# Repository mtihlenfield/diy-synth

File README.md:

# Library of DIY Eurorack Modules

## Completed Modules:

- mixer - Simple buffered mixer
- mulitple - Simple buffered multiple
- noise - Noise generater module - Based on moritz klien's design
- keyboard - Volt per octave keyboard and sequencer
- power-supply - -+12V power supply

## In progress

- Attenuverter
- VCLFO

## Future Modules:

- quantizer - Digital quantizer
- Sample and Hold
- Slew Limiter

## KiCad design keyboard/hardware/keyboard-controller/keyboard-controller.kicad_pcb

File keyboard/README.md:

# CV/Gate Keyboard

An attempt at implementing a CV/Gate keyboard using a raspberry pi pico and an old keybed from a Yamaha PSS-560

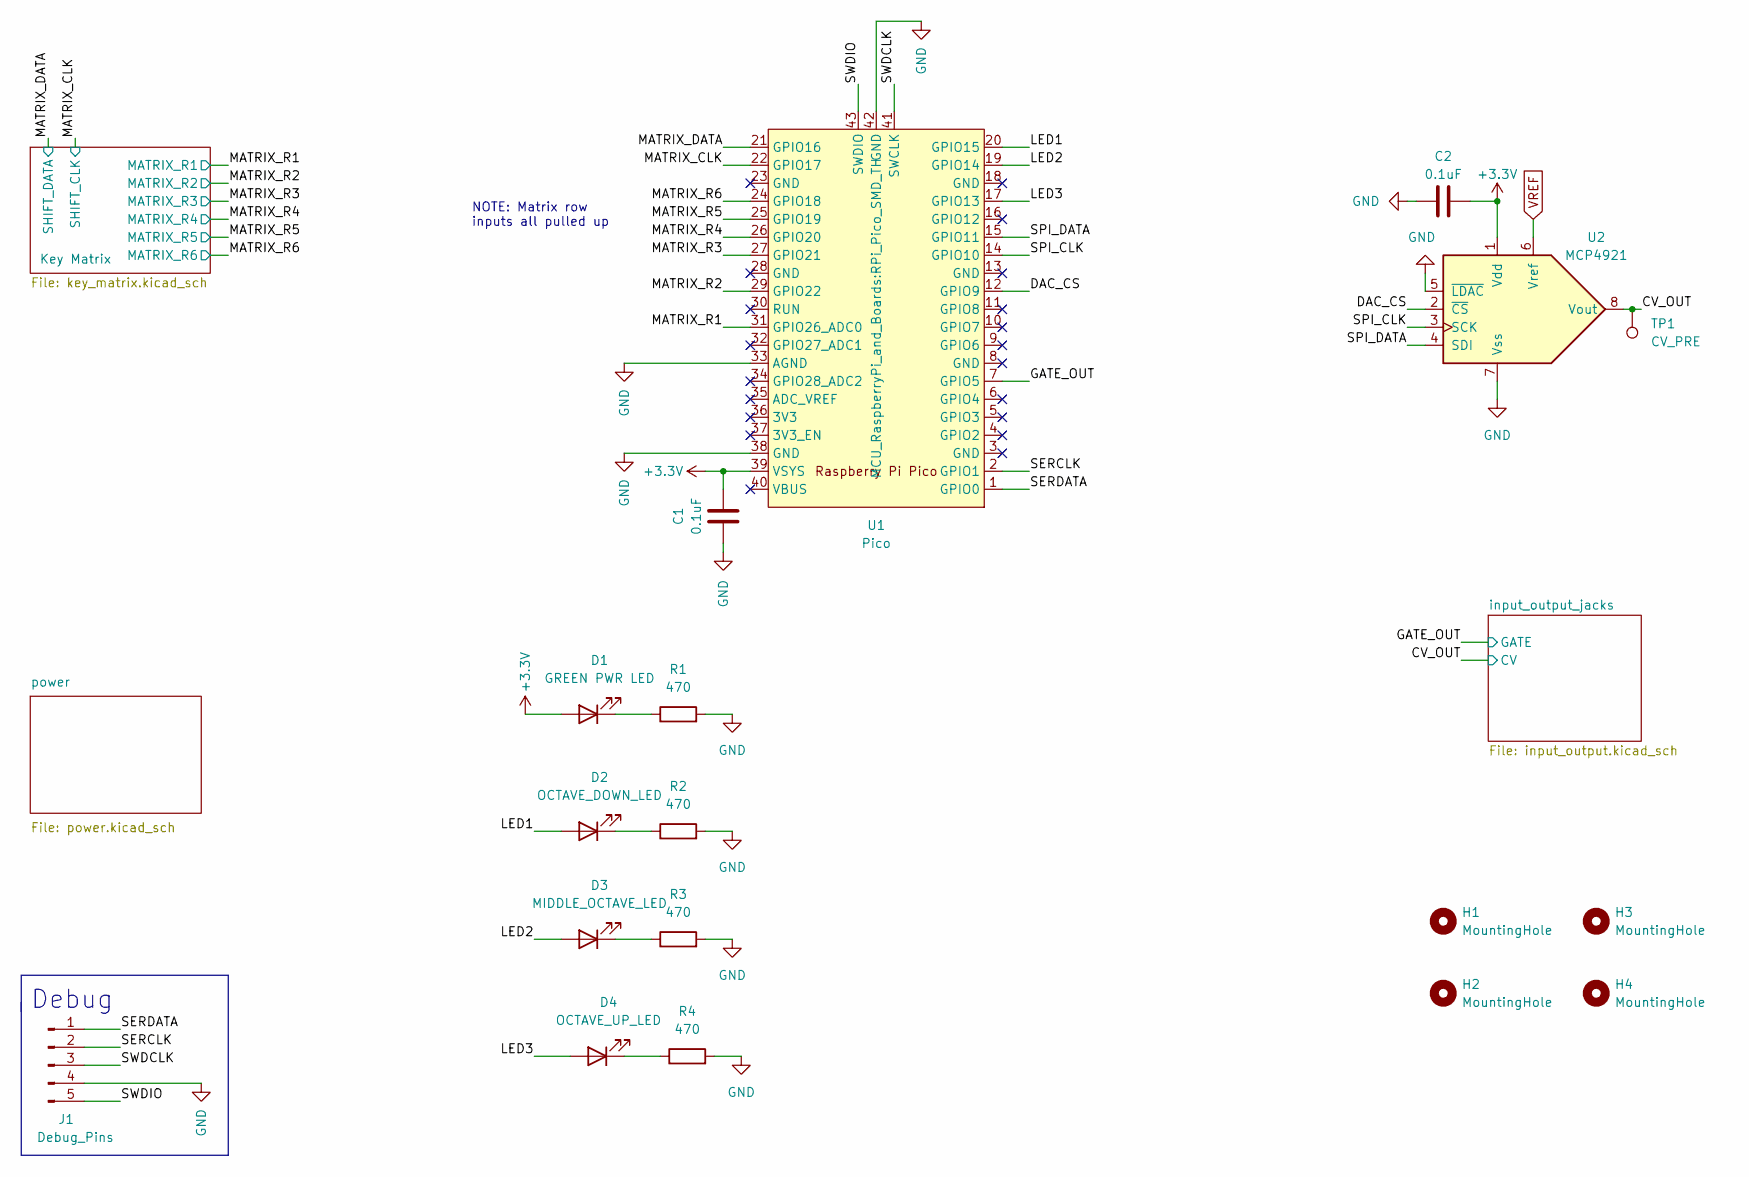
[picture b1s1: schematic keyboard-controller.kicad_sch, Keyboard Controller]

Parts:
C1, C2: 0.1uF; C_Disc_D5.0mm_W2.5mm_P3.0mm; Manufacturer Part No. 0.1uF 50V Ceramic Disc Capacitor
D1: GREEN PWR LED; LED_D5.0mm; Manufacturer Part No. LED 5mm Green
D2: OCTAVE_DOWN_LED; LED_D5.0mm; Manufacturer Part No. C503B-RAN-CZ0C0AA1
D3: MIDDLE_OCTAVE_LED; LED_D5.0mm; Manufacturer Part No. C503B-RAN-CZ0C0AA1
D4: OCTAVE_UP_LED; LED_D5.0mm; Manufacturer Part No. C503B-RAN-CZ0C0AA1
H1, H2, H3, H4: MountingHole; MountingHole_3.2mm_M3; Manufacturer Part No. N/A
J1: Debug_Pins; PinHeader_1x05_P2.54mm_Vertical; Manufacturer Part No. PHSS05G10
R1, R2, R3, R4: 470; R_Axial_DIN0207_L6.8mm_D2.5mm_P10.16mm_Horizontal; Manufacturer Part No. MF0W4FF4700A50
TP1: CV_PRE; TestPoint_Pad_D1.5mm
U1: Pico; RPi_Pico_SMD_TH; Manufacturer Part No. SC0915
U2: MCP4921; DIP-8_W7.62mm_Socket; Manufacturer Part No. MCP4921-E/P

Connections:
+3.3V: C1.2, C2.2, D1.2 (A), U1.39 (VSYS), U2.1 (Vdd); also elsewhere on the board
/CV_OUT: TP1.1, U2.8 (Vout); also elsewhere on the board
/DAC_CS: U1.12 (GPIO9), U2.2 (~CS)
/GATE_OUT: U1.7 (GPIO5); also elsewhere on the board
/LED1: D2.2 (A), U1.20 (GPIO15)
/LED2: D3.2 (A), U1.19 (GPIO14)
/LED3: D4.2 (A), U1.17 (GPIO13)
/MATRIX_CLK: U1.22 (GPIO17); also elsewhere on the board
/MATRIX_DATA: U1.21 (GPIO16); also elsewhere on the board
/MATRIX_R1: U1.31 (GPIO26_ADC0); also elsewhere on the board
/MATRIX_R2: U1.29 (GPIO22); also elsewhere on the board
/MATRIX_R3: U1.27 (GPIO21); also elsewhere on the board
/MATRIX_R4: U1.26 (GPIO20); also elsewhere on the board
/MATRIX_R5: U1.25 (GPIO19); also elsewhere on the board
/MATRIX_R6: U1.24 (GPIO18); also elsewhere on the board
/SERCLK: J1.2, U1.2 (GPIO1)
/SERDATA: J1.1, U1.1 (GPIO0)
/SPI_CLK: U1.14 (GPIO10), U2.3 (SCK)
/SPI_DATA: U1.15 (GPIO11), U2.4 (SDI)
/SWDCLK: J1.3, U1.41 (SWCLK)
/SWDIO: J1.5, U1.43 (SWDIO)
GND: C1.1, C2.1, J1.4, R1.2, R2.2, R3.2, R4.2, U1.33 (AGND), U1.38 (GND), U1.42 (GND), U2.5 (~LDAC), U2.7 (Vss); also elsewhere on the board
unnamed: D1.1 (K), R1.1
unnamed: D2.1 (K), R2.1
unnamed: D3.1 (K), R3.1
unnamed: D4.1 (K), R4.1
VREF: U2.6 (Vref); also elsewhere on the board

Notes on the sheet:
NOTE: Matrix row inputs all pulled up
Debug

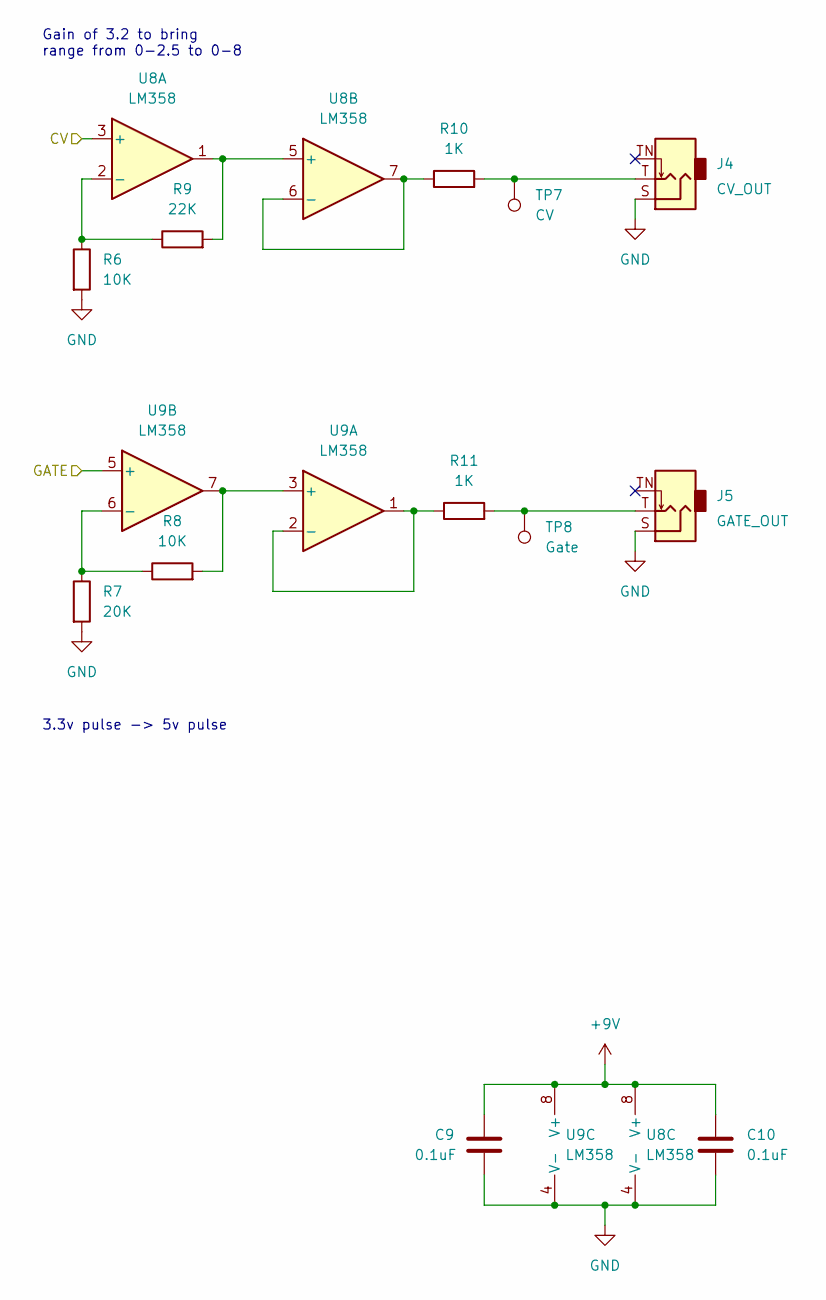
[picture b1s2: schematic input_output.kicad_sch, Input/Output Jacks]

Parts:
C9, C10: 0.1uF; C_Disc_D5.0mm_W2.5mm_P3.0mm; Manufacturer Part No. 0.1uF 50V Ceramic Disc Capacitor
J4: CV_OUT; Jack_3.5mm_QingPu_WQP-PJ398SM_Vertical; Manufacturer Part No. PJ-629HAN-05
J5: GATE_OUT; Jack_3.5mm_QingPu_WQP-PJ398SM_Vertical; Manufacturer Part No. PJ-629HAN-05
R6, R8: 10K; R_Axial_DIN0207_L6.8mm_D2.5mm_P10.16mm_Horizontal; Manufacturer Part No. MF0W4FF1002A50
R7: 20K; R_Axial_DIN0207_L6.8mm_D2.5mm_P10.16mm_Horizontal; Manufacturer Part No. MF0W4FF2002A50
R9: 22K; R_Axial_DIN0207_L6.8mm_D2.5mm_P10.16mm_Horizontal; Manufacturer Part No. MF0W4FF2202A50
R10, R11: 1K; R_Axial_DIN0207_L6.8mm_D2.5mm_P10.16mm_Horizontal; Manufacturer Part No. MF0W4FF1001A50
TP7: CV; TestPoint_Pad_D1.5mm
TP8: Gate; TestPoint_Pad_D1.5mm
U8, U9: LM358; DIP-8_W7.62mm_Socket; Manufacturer Part No. LM358P

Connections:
+9V: C9.1, C10.1, U8.8 (V+), U9.8 (V+); also elsewhere on the board
/CV_OUT: U8.3 (+); also elsewhere on the board
/GATE_OUT: U9.5 (+); also elsewhere on the board
GND: C9.2, C10.2, J4.S, J5.S, R6.2, R7.2, U8.4 (V-), U9.4 (V-); also elsewhere on the board
unnamed: J4.T, R10.2, TP7.1
unnamed: J5.T, R11.2, TP8.1
unnamed: R6.1, R9.1, U8.2 (-)
unnamed: R7.1, R8.1, U9.6 (-)
unnamed: R8.2, U9.3 (+), U9.7
unnamed: R9.2, U8.1, U8.5 (+)
unnamed: R10.1, U8.6 (-), U8.7
unnamed: R11.1, U9.1, U9.2 (-)

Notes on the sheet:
3.3v pulse -> 5v pulse
Gain of 3.2 to bring range from 0-2.5 to 0-8

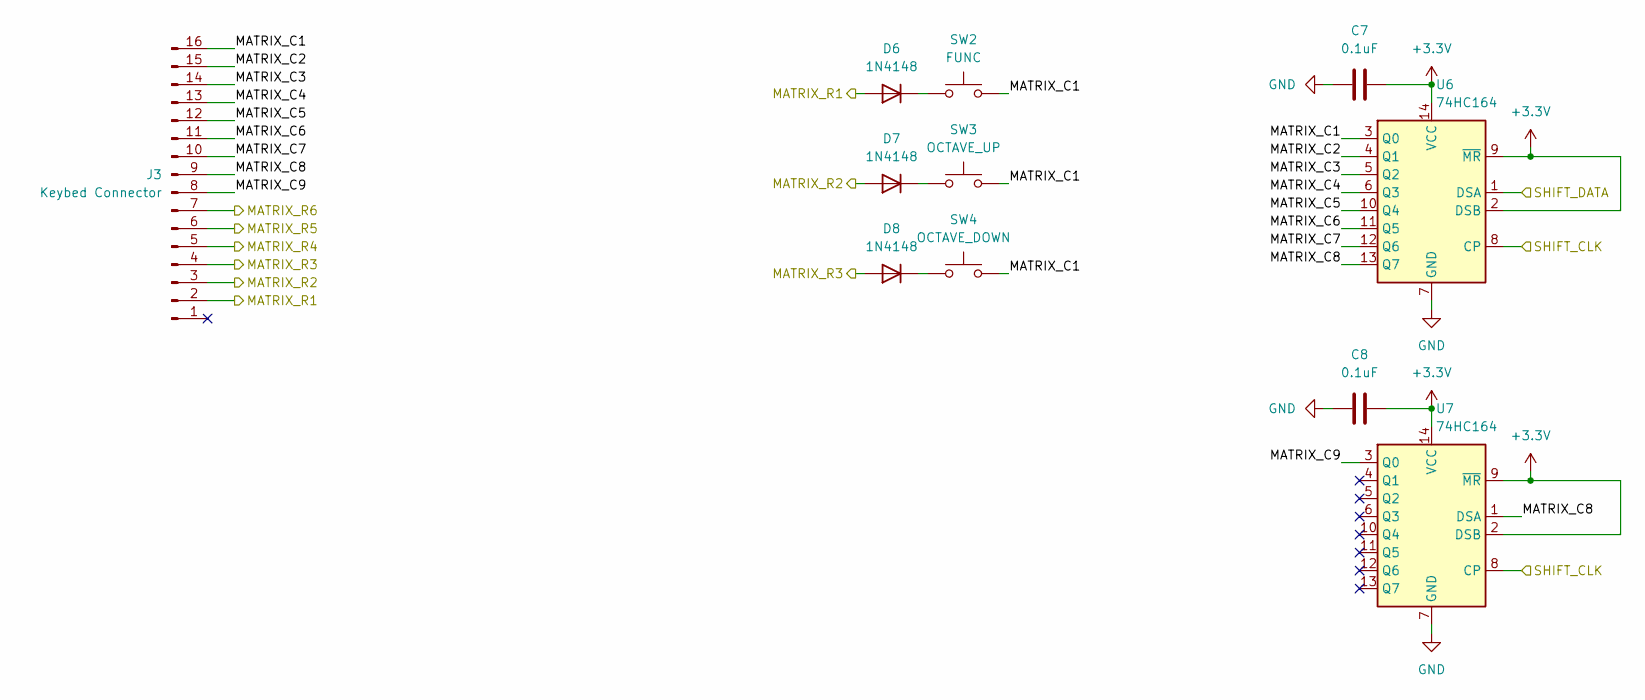
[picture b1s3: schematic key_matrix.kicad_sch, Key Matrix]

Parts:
C7, C8: 0.1uF; C_Disc_D5.0mm_W2.5mm_P3.0mm; Manufacturer Part No. 0.1uF 50V Ceramic Disc Capacitor
D6, D7, D8: 1N4148; D_DO-35_SOD27_P7.62mm_Horizontal; Manufacturer Part No. 1N4148
J3: Keybed Connector; IDC-Header_2x08_P2.54mm_Vertical; Manufacturer Part No. BHD16PHZT
SW2: FUNC; SW_PUSH_6mm; Manufacturer Part No. Tact Switch 6x6mm 5mm
SW3: OCTAVE_UP; SW_PUSH_6mm; Manufacturer Part No. Tact Switch 6x6mm 5mm
SW4: OCTAVE_DOWN; SW_PUSH_6mm; Manufacturer Part No. Tact Switch 6x6mm 5mm
U6, U7: 74HC164; DIP-14_W7.62mm_Socket; Manufacturer Part No. SN74HC164N

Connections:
+3.3V: C7.2, C8.2, U6.2 (DSB), U6.9 (~MR), U6.14 (VCC), U7.2 (DSB), U7.9 (~MR), U7.14 (VCC); also elsewhere on the board
/Key Matrix/MATRIX_C1: J3.16, SW2.2, SW3.2, SW4.2, U6.3 (Q0)
/Key Matrix/MATRIX_C2: J3.15, U6.4 (Q1)
/Key Matrix/MATRIX_C3: J3.14, U6.5 (Q2)
/Key Matrix/MATRIX_C4: J3.13, U6.6 (Q3)
/Key Matrix/MATRIX_C5: J3.12, U6.10 (Q4)
/Key Matrix/MATRIX_C6: J3.11, U6.11 (Q5)
/Key Matrix/MATRIX_C7: J3.10, U6.12 (Q6)
/Key Matrix/MATRIX_C8: J3.9, U6.13 (Q7), U7.1 (DSA)
/Key Matrix/MATRIX_C9: J3.8, U7.3 (Q0)
/MATRIX_CLK: U6.8 (CP), U7.8 (CP); also elsewhere on the board
/MATRIX_DATA: U6.1 (DSA); also elsewhere on the board
/MATRIX_R1: D6.2 (A), J3.2; also elsewhere on the board
/MATRIX_R2: D7.2 (A), J3.3; also elsewhere on the board
/MATRIX_R3: D8.2 (A), J3.4; also elsewhere on the board
/MATRIX_R4: J3.5; also elsewhere on the board
/MATRIX_R5: J3.6; also elsewhere on the board
/MATRIX_R6: J3.7; also elsewhere on the board
GND: C7.1, C8.1, U6.7 (GND), U7.7 (GND); also elsewhere on the board
unnamed: D6.1 (K), SW2.1
unnamed: D7.1 (K), SW3.1
unnamed: D8.1 (K), SW4.1

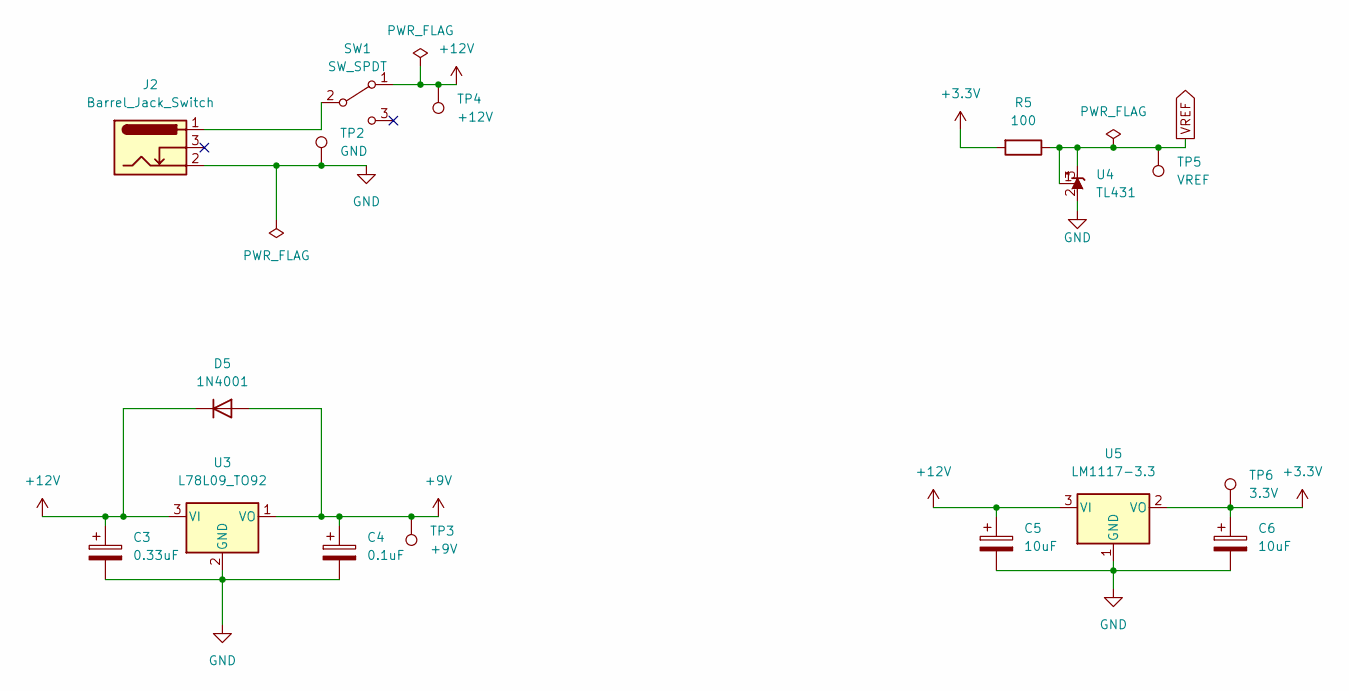
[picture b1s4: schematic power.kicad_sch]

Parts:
C3: 0.33uF; CP_Radial_Tantal_D4.5mm_P2.50mm; Manufacturer Part No. 0.33uF 35V Radial Capacitor Tantalum
C4: 0.1uF; CP_Radial_Tantal_D4.5mm_P2.50mm; Manufacturer Part No. 0.1uF 35V Radial Capacitor Tantalum
C5, C6: 10uF; CP_Radial_Tantal_D4.5mm_P2.50mm; Manufacturer Part No. 10uF 35V Radial Capacitor Tantalum
D5: 1N4001; D_DO-41_SOD81_P10.16mm_Horizontal; Manufacturer Part No. 1N4001
J2: Barrel_Jack_Switch; BarrelJack_Horizontal_2.1mm_WEALTH_METAL; Manufacturer Part No. DC Power Jack 2.1mm
R5: 100; R_Axial_DIN0207_L6.8mm_D2.5mm_P10.16mm_Horizontal; Manufacturer Part No. MF0W4FF1000A50
SW1: SW_SPDT; Slide_Switch_SPDT_SS12F44G5; Manufacturer Part No. SS12F44G5
TP2: GND; TestPoint_Pad_D1.5mm
TP3: +9V; TestPoint_Pad_D1.5mm
TP4: +12V; TestPoint_Pad_D1.5mm
TP5: VREF; TestPoint_Pad_D1.5mm
TP6: 3.3V; TestPoint_Pad_D1.5mm
U3: L78L09_TO92; TO-92_Inline
U4: TL431; TO-92_Inline; Manufacturer Part No. TL431ACL
U5: LM1117-3.3; TO-220-3_Horizontal_TabDown; Manufacturer Part No. LM1117T

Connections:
+3.3V: C6.1, R5.2, TP6.1, U5.2 (VO); also elsewhere on the board
+9V: C4.1, D5.2 (A), TP3.1, U3.1 (VO); also elsewhere on the board
+12V: C3.1, C5.1, D5.1 (K), SW1.1 (A), TP4.1, U3.3 (VI), U5.3 (VI)
GND: C3.2, C4.2, C5.2, C6.2, J2.2, TP2.1, U3.2 (GND), U4.2 (A), U5.1 (GND); also elsewhere on the board
unnamed: J2.1, SW1.2 (B)
VREF: R5.1, TP5.1, U4.1 (REF), U4.3 (K); also elsewhere on the board

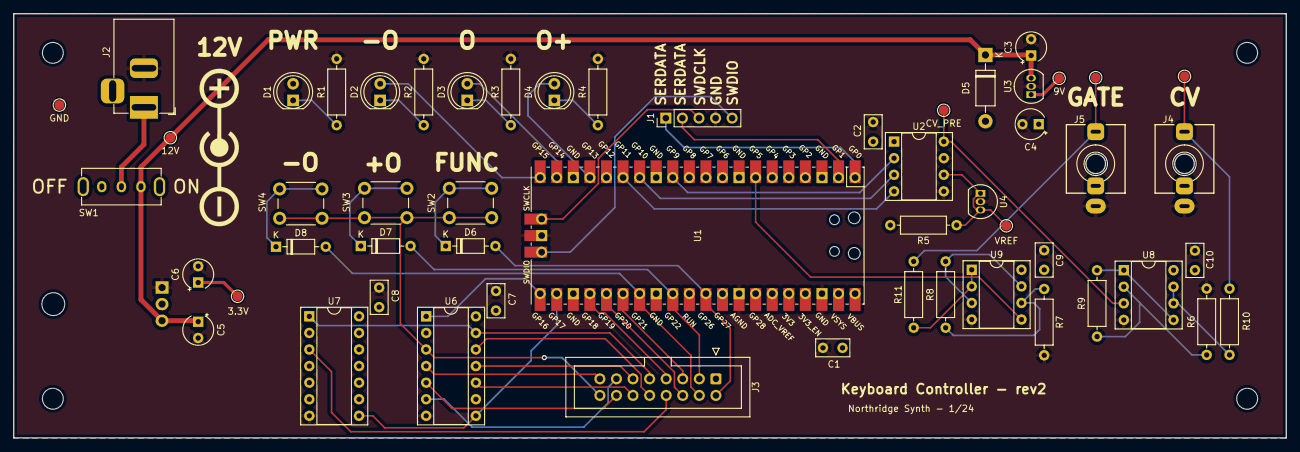
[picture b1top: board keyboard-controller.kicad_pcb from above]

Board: 2 copper layers, 195.0 x 65.0 mm, 59 parts (1 on the bottom side), 50 nets.

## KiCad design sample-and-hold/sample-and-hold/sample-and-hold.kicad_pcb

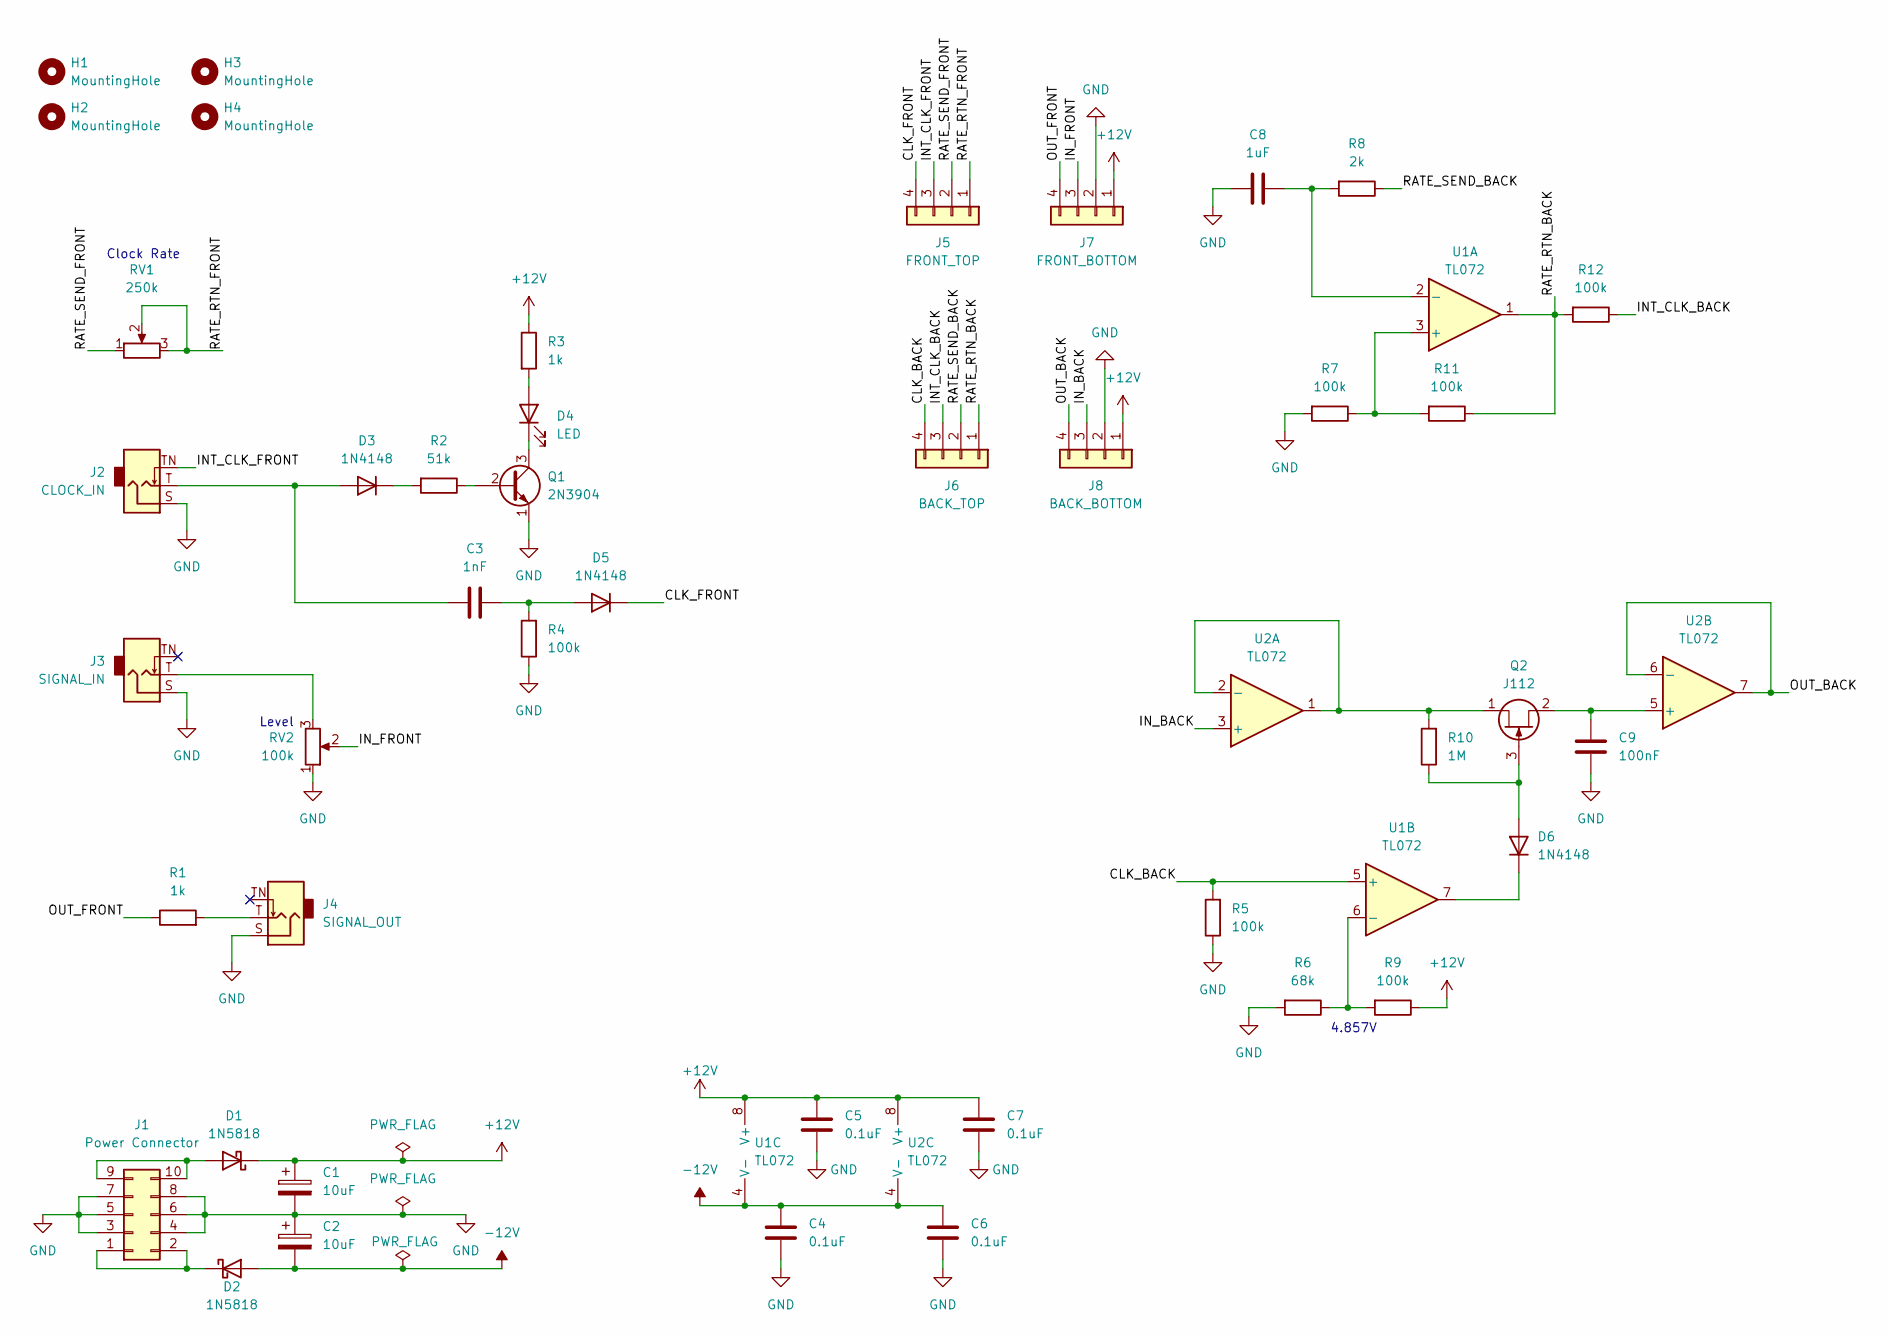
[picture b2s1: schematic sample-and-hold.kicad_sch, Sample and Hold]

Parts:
C1, C2: 10uF; CP_Radial_D5.0mm_P2.00mm; Manufacturer Part No. WK1CM100D11OT
C3: 1nF; C_Rect_L7.2mm_W2.5mm_P5.00mm_FKS2_FKP2_MKS2_MKP2; Manufacturer Part No. R82EC1100AA50J
C4, C5, C6, C7: 0.1uF; C_Disc_D5.0mm_W2.5mm_P2.50mm; Manufacturer Part No. 0.1uF 50V Ceramic Disc Capacitor
C8: 1uF; C_Rect_L7.2mm_W3.5mm_P5.00mm_FKS2_FKP2_MKS2_MKP2; Manufacturer Part No. MKS2B041001C00KSSD
C9: 100nF; C_Rect_L7.2mm_W2.5mm_P5.00mm_FKS2_FKP2_MKS2_MKP2; Manufacturer Part No. R82EC3100DQ70J
D1, D2: 1N5818; D_DO-41_SOD81_P10.16mm_Horizontal; Manufacturer Part No. 1N5817
D3, D5, D6: 1N4148; D_DO-35_SOD27_P7.62mm_Horizontal; Manufacturer Part No. 1N4148
D4: LED; LED_D3.0mm; Manufacturer Part No. LED 3mm Red
H1, H2, H3, H4: MountingHole; MountingHole_2.2mm_M2
J1: Power Connector; IDC-Header_2x05_P2.54mm_Vertical; Manufacturer Part No. BHD10PHZT
J2: CLOCK_IN; Jack_3.5mm_QingPu_WQP-PJ398SM_Vertical; Manufacturer Part No. PJ-3001F
J3: SIGNAL_IN; Jack_3.5mm_QingPu_WQP-PJ398SM_Vertical; Manufacturer Part No. PJ-3001F
J4: SIGNAL_OUT; Jack_3.5mm_QingPu_WQP-PJ398SM_Vertical; Manufacturer Part No. PJ-3001F
J5: FRONT_TOP; PinHeader_1x04_P2.54mm_Vertical; Manufacturer Part No. 4 Female Pin Header
J6: BACK_TOP; PinHeader_1x04_P2.54mm_Vertical; Manufacturer Part No. PHSS12G10
J7: FRONT_BOTTOM; PinHeader_1x04_P2.54mm_Vertical; Manufacturer Part No. 4 Female Pin Header
J8: BACK_BOTTOM; PinHeader_1x04_P2.54mm_Vertical; Manufacturer Part No. PHSS12G10
Q1: 2N3904; TO-92_Inline; Manufacturer Part No. 2N3904
Q2: J112; TO-92; Manufacturer Part No. J112
R1, R3: 1k; R_Axial_DIN0207_L6.3mm_D2.5mm_P10.16mm_Horizontal; Manufacturer Part No. MF0W4FF1001A50
R2: 51k; R_Axial_DIN0207_L6.3mm_D2.5mm_P10.16mm_Horizontal; Manufacturer Part No. MF0W4FF5102A50
R4, R5, R7, R9, R11, R12: 100k; R_Axial_DIN0207_L6.3mm_D2.5mm_P10.16mm_Horizontal; Manufacturer Part No. MF0W4FF1003A50
R6: 68k; R_Axial_DIN0207_L6.3mm_D2.5mm_P10.16mm_Horizontal; Manufacturer Part No. MF0W4FF6802A50
R8: 2k; R_Axial_DIN0207_L6.3mm_D2.5mm_P10.16mm_Horizontal; Manufacturer Part No. MF0W4FF2001A50
R10: 1M; R_Axial_DIN0207_L6.3mm_D2.5mm_P10.16mm_Horizontal; Manufacturer Part No. MF0W4FF1004A50
RV1: 250k; Potentiometer_Alpha_RV09AF-40-20K_Single_Vertical; Manufacturer Part No. RV09AF-40-20K-B250K
RV2: 100k; Potentiometer_Alpha_RV09AF-40-20K_Single_Vertical; Manufacturer Part No. RV09AF-40-20K-B100K
U1, U2: TL072; DIP-8_W7.62mm_Socket; Manufacturer Part No. TL072CP

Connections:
+12V: C1.1, C5.1, C7.1, D1.1 (K), J7.1, J8.1, R3.1, R9.1, U1.8 (V+), U2.8 (V+)
-12V: C2.2, C4.1, C6.1, D2.2 (A), U1.4 (V-), U2.4 (V-)
/CLK_BACK: J6.4, R5.2, U1.5 (+)
/CLK_FRONT: D5.1 (K), J5.4; also elsewhere on the board
/INT_CLK_BACK: J6.3, R12.1
/INT_CLK_FRONT: J2.TN, J5.3; also elsewhere on the board
/IN_BACK: J8.3, U2.3 (+)
/IN_FRONT: J7.3, RV2.2
/OUT_BACK: J8.4, U2.6 (-), U2.7
/OUT_FRONT: J7.4, R1.1
/RATE_RTN_BACK: J6.1, R11.1, R12.2, U1.1
/RATE_RTN_FRONT: J5.1, RV1.2, RV1.3; also elsewhere on the board
/RATE_SEND_BACK: J6.2, R8.1
/RATE_SEND_FRONT: J5.2, RV1.1; also elsewhere on the board
GND: C1.2, C2.1, C4.2, C5.2, C6.2, C7.2, C8.1, C9.1, J1.3, J1.4, J1.5, J1.6, J1.7, J1.8, J2.S, J3.S, J4.S, J7.2, J8.2, Q1.1 (E), R4.1, R5.1, R6.2, R7.2, RV2.1
unnamed: C3.1, D3.2 (A), J2.T
unnamed: C3.2, D5.2 (A), R4.2
unnamed: C8.2, R8.2, U1.2 (-)
unnamed: C9.2, Q2.2 (S), U2.5 (+)
unnamed: D1.2 (A), J1.9, J1.10
unnamed: D2.1 (K), J1.1, J1.2
unnamed: D3.1 (K), R2.2
unnamed: D4.1 (K), Q1.3 (C)
unnamed: D4.2 (A), R3.2
unnamed: D6.1 (K), U1.7
unnamed: D6.2 (A), Q2.3 (G), R10.1
unnamed: J3.T, RV2.3
unnamed: J4.T, R1.2
unnamed: Q1.2 (B), R2.1
unnamed: Q2.1 (D), R10.2, U2.1, U2.2 (-)
unnamed: R6.1, R9.2, U1.6 (-)
unnamed: R7.1, R11.2, U1.3 (+)

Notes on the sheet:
Clock Rate
Level
4.857V

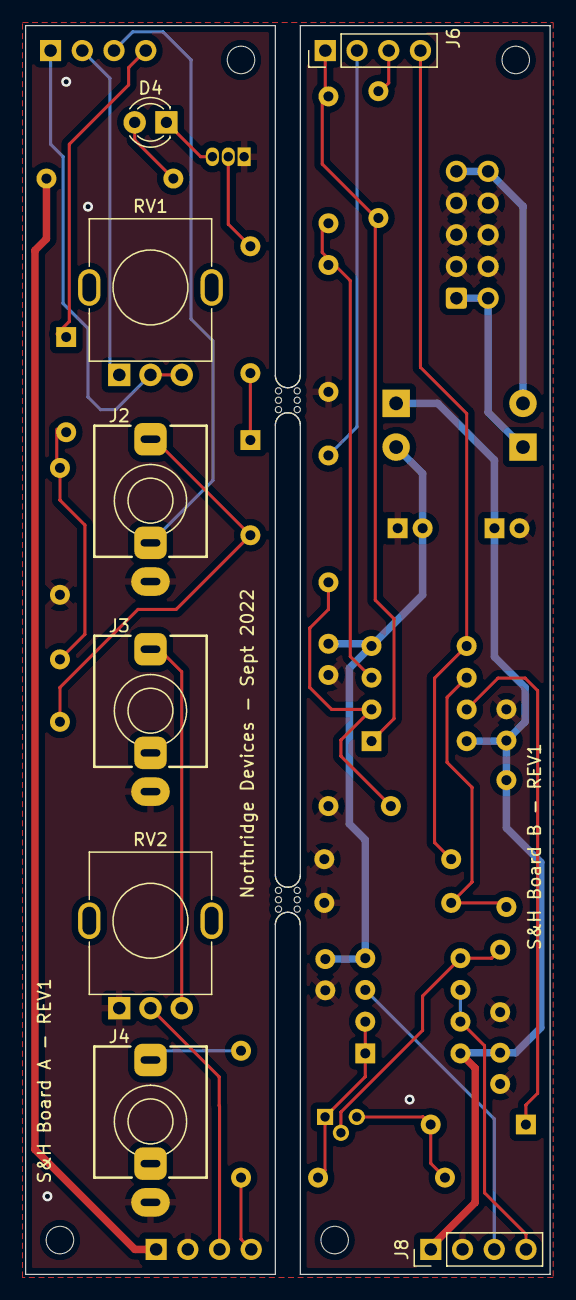
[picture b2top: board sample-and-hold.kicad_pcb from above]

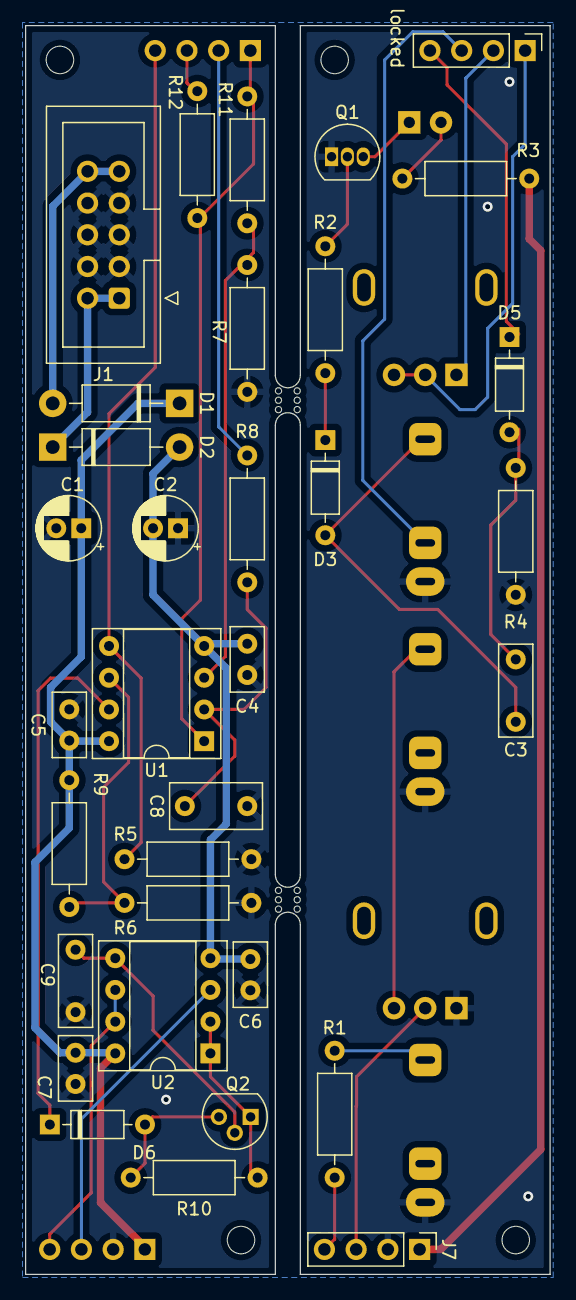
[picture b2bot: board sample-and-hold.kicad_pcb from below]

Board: 2 copper layers, 42.0 x 100.0 mm, 47 parts (33 on the bottom side), 32 nets.

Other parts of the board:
locked: FRONT_TOP; PinHeader_1x04_P2.54mm_Vertical
mouse-bite-2mm-slot, mouse-bite-2mm-slot#2: VAL**; mouse-bite-2mm-slot

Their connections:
/CLK_FRONT: locked.4; also elsewhere on the board
/INT_CLK_FRONT: locked.3; also elsewhere on the board
/RATE_RTN_FRONT: locked.1; also elsewhere on the board
/RATE_SEND_FRONT: locked.2; also elsewhere on the board

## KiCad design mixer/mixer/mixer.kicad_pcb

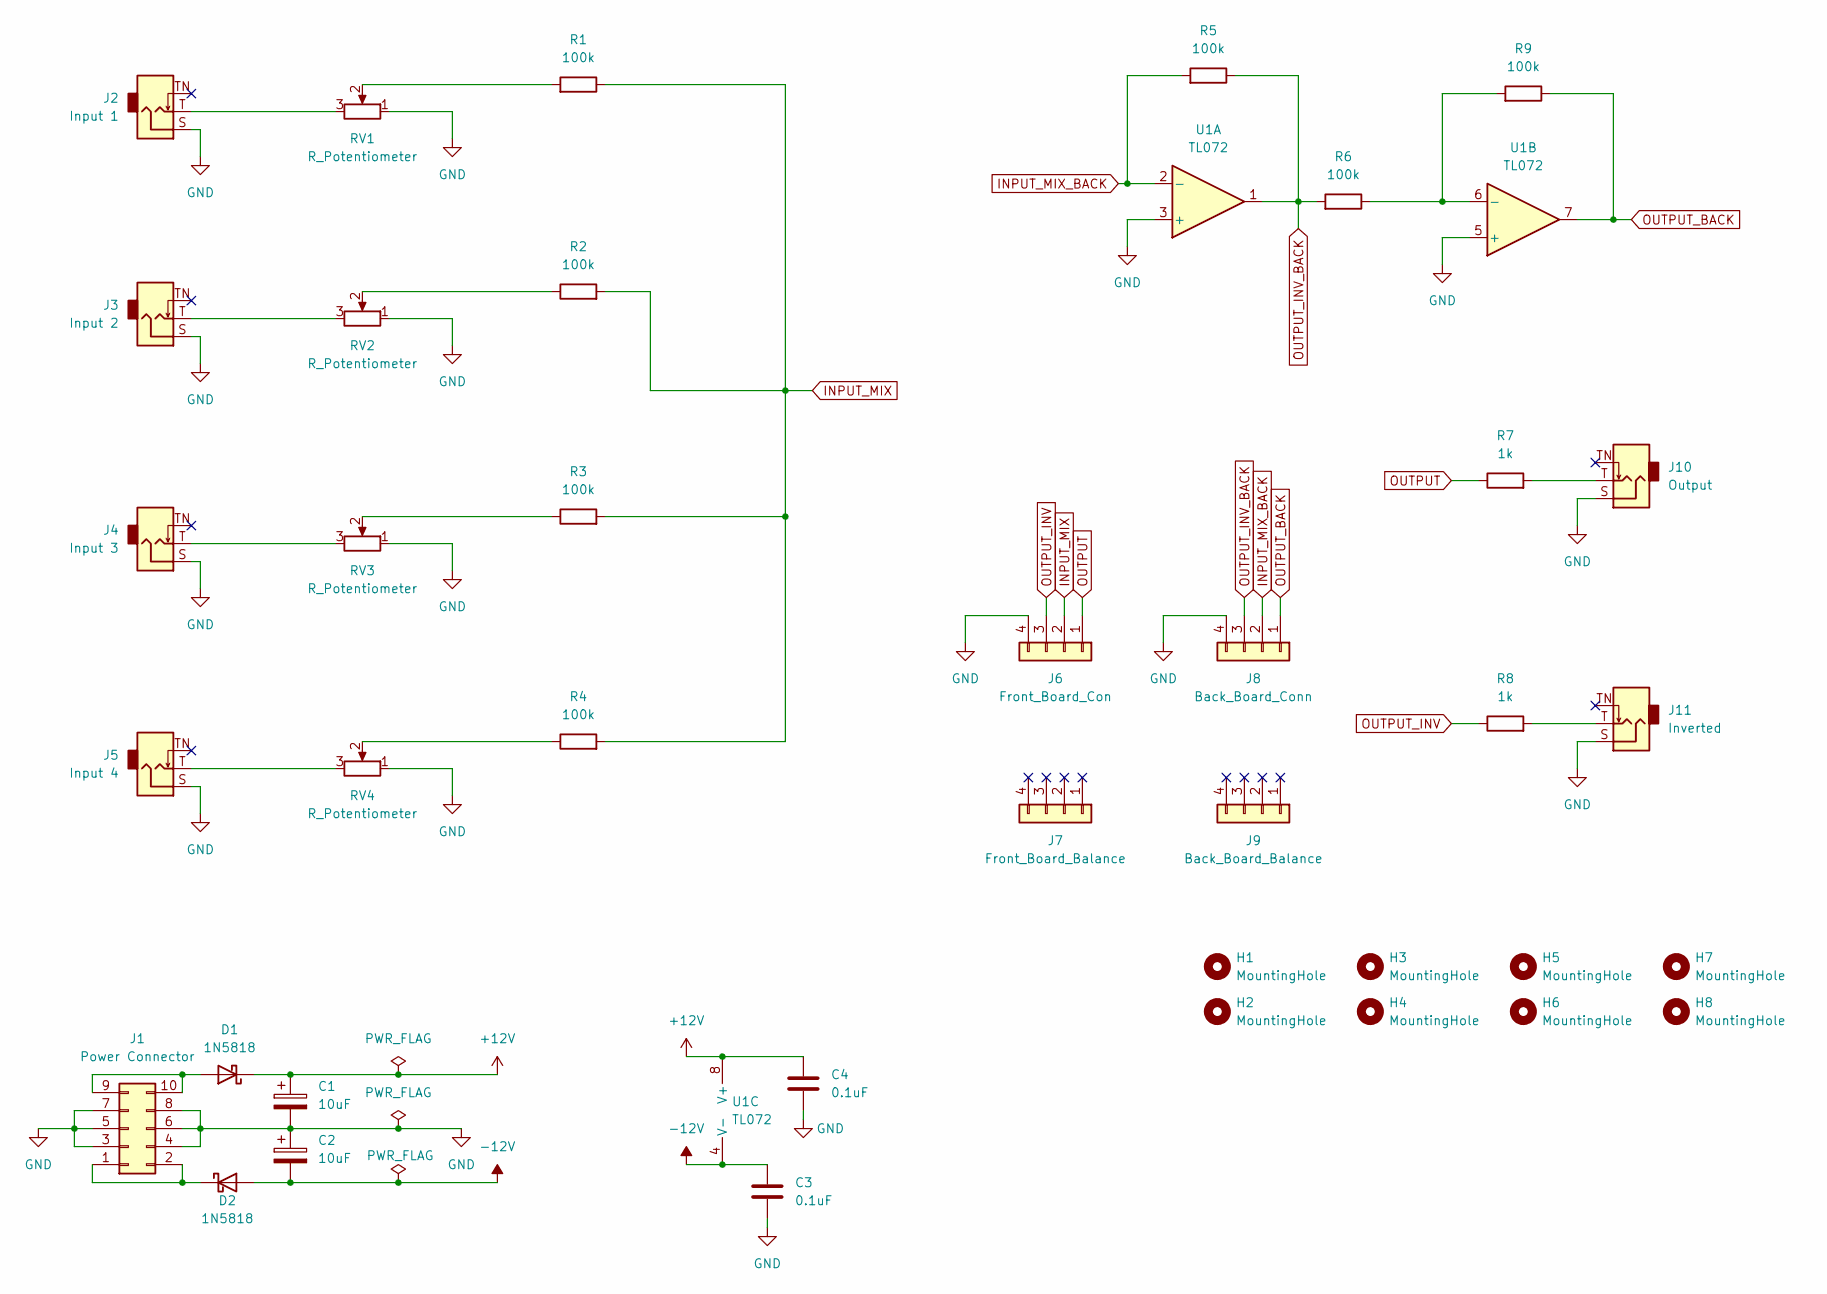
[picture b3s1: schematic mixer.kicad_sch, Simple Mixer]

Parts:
C1, C2: 10uF; CP_Radial_D5.0mm_P2.00mm; Manufacturer Part No. WK1CM100D11OT
C3, C4: 0.1uF; C_Disc_D5.0mm_W2.5mm_P2.50mm; Manufacturer Part No. 0.1uF 50V Ceramic Disc Capacitor
D1, D2: 1N5818; D_DO-41_SOD81_P10.16mm_Horizontal; Manufacturer Part No. 1N5817
H1, H2, H3, H4, H5, H6, H7, H8: MountingHole; MountingHole_2.2mm_M2
J1: Power Connector; IDC-Header_2x05_P2.54mm_Vertical; Manufacturer Part No. BHD10PHZT
J2: Input 1; Jack_3.5mm_QingPu_WQP-PJ398SM_Vertical; Manufacturer Part No. PJ-3001F
J3: Input 2; Jack_3.5mm_QingPu_WQP-PJ398SM_Vertical; Manufacturer Part No. PJ-3001F
J4: Input 3; Jack_3.5mm_QingPu_WQP-PJ398SM_Vertical; Manufacturer Part No. PJ-3001F
J5: Input 4; Jack_3.5mm_QingPu_WQP-PJ398SM_Vertical; Manufacturer Part No. PJ-3001F
J6: Front_Board_Con; PinHeader_1x04_P2.54mm_Vertical; Manufacturer Part No. 4 Female Pin Header
J7: Front_Board_Balance; PinHeader_1x04_P2.54mm_Vertical; Manufacturer Part No. 4 Female Pin Header
J8: Back_Board_Conn; PinHeader_1x04_P2.54mm_Vertical; Manufacturer Part No. PHSS12G10
J9: Back_Board_Balance; PinHeader_1x04_P2.54mm_Vertical; Manufacturer Part No. PHSS12G10
J10: Output; Jack_3.5mm_QingPu_WQP-PJ398SM_Vertical; Manufacturer Part No. PJ-3001F
J11: Inverted; Jack_3.5mm_QingPu_WQP-PJ398SM_Vertical; Manufacturer Part No. PJ-3001F
R1, R2, R3, R4, R5, R6, R9: 100k; R_Axial_DIN0207_L6.3mm_D2.5mm_P10.16mm_Horizontal; Manufacturer Part No. MF0W4FF1003A50
R7, R8: 1k; R_Axial_DIN0207_L6.3mm_D2.5mm_P10.16mm_Horizontal; Manufacturer Part No. MF0W4FF1001A50
RV1, RV2, RV3, RV4: R_Potentiometer; Potentiometer_Alpha_RV09AF-40-20K_Single_Vertical; Manufacturer Part No. RV09AF-40-20K-B100K
U1: TL072; DIP-8_W7.62mm_Socket; Manufacturer Part No. TL072CP

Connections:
+12V: C1.1, C4.1, D1.1 (K), U1.8 (V+)
-12V: C2.2, C3.1, D2.2 (A), U1.4 (V-)
GND: C1.2, C2.1, C3.2, C4.2, J1.3, J1.4, J1.5, J1.6, J1.7, J1.8, J2.S, J3.S, J4.S, J5.S, J6.4, J8.4, J10.S, J11.S, RV1.1, RV2.1, RV3.1, RV4.1, U1.3 (+), U1.5 (+)
INPUT_MIX: J6.2, R1.1, R2.2, R3.2, R4.2
INPUT_MIX_BACK: J8.2, R5.2, U1.2 (-)
unnamed: D1.2 (A), J1.9, J1.10
unnamed: D2.1 (K), J1.1, J1.2
unnamed: J2.T, RV1.3
unnamed: J3.T, RV2.3
unnamed: J4.T, RV3.3
unnamed: J5.T, RV4.3
unnamed: J10.T, R7.2
unnamed: J11.T, R8.2
unnamed: R1.2, RV1.2
unnamed: R2.1, RV2.2
unnamed: R3.1, RV3.2
unnamed: R4.1, RV4.2
unnamed: R6.1, R9.2, U1.6 (-)
OUTPUT: J6.1, R7.1
OUTPUT_BACK: J8.1, R9.1, U1.7
OUTPUT_INV: J6.3, R8.1
OUTPUT_INV_BACK: J8.3, R5.1, R6.2, U1.1
